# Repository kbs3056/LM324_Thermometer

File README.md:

# LM324_Thermometer

Small four LEDs NTC thermometer. Only one LED is turned on at a time.

LED1=>50°C, LED2=>60°C, LED3=>70°C, LED4=>80°C, 
Or you can calculate your own values with an included spreadsheet.

https://www.youtube.com/watch?v=8DjqupTEYBM

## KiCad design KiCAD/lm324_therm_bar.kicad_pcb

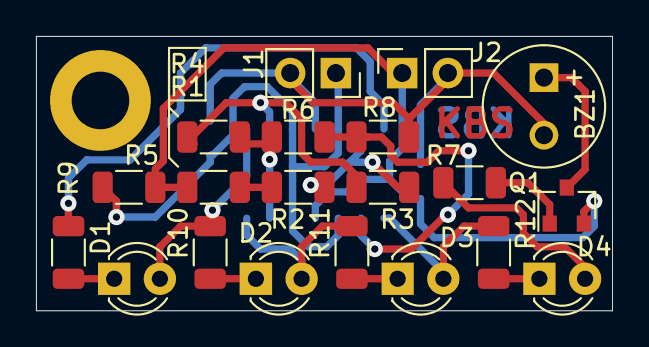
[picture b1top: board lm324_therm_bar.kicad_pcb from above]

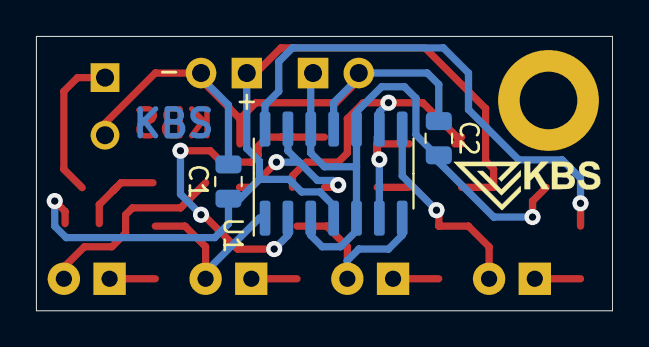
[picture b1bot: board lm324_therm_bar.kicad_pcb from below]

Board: 2 copper layers, 32.0 x 15.2 mm, 23 parts (3 on the bottom side), 19 nets.

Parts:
BZ1: Buzzer; MagneticBuzzer_Kingstate_KCG0601
C1: 1u; C_0805_2012Metric
C2: 100n; C_0805_2012Metric
D1, D2, D3, D4: LED; LED_D3.0mm
J1: NTC100k; PinSocket_1x02_P2.54mm_Vertical
J2: supl.; PinSocket_1x02_P2.54mm_Vertical
Q1: MMBT3906; SOT-23
R1: 2k7; R_1206_3216Metric
R2: 2k2; R_1206_3216Metric
R3: 1k2; R_1206_3216Metric
R4: 1k1; R_1206_3216Metric
R5: 22k; R_1206_3216Metric
R6, R7: 1k; R_1206_3216Metric
R8: 4k7; R_1206_3216Metric
R9, R10, R11, R12: 3k3; R_1206_3216Metric
U1: LM324; SOIC-14_3.9x8.7mm_P1.27mm

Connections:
+5V: C1.1, J2.1, Q1.2, R1.1, R5.1, U1.4
GND: BZ1.2, C1.2, C2.1, J1.2, J2.2, R8.2, U1.11
unnamed: BZ1.1, Q1.3
unnamed: C2.2, J1.1, R5.2, U1.3, U1.5, U1.10, U1.12
unnamed: D1.1, R9.1
unnamed: D1.2, R10.2, U1.8
unnamed: D2.1, R10.1
unnamed: D2.2, R11.2, U1.7
unnamed: D3.1, R11.1
unnamed: D3.2, R12.2, U1.1
unnamed: D4.1, R12.1
unnamed: D4.2, R7.2
unnamed: Q1.1, R7.1
unnamed: R1.2, R2.1
unnamed: R2.2, R3.1, U1.13
unnamed: R3.2, R4.1, U1.9
unnamed: R4.2, R6.1, U1.6
unnamed: R6.2, R8.1, U1.2
unnamed: R9.2, U1.14
